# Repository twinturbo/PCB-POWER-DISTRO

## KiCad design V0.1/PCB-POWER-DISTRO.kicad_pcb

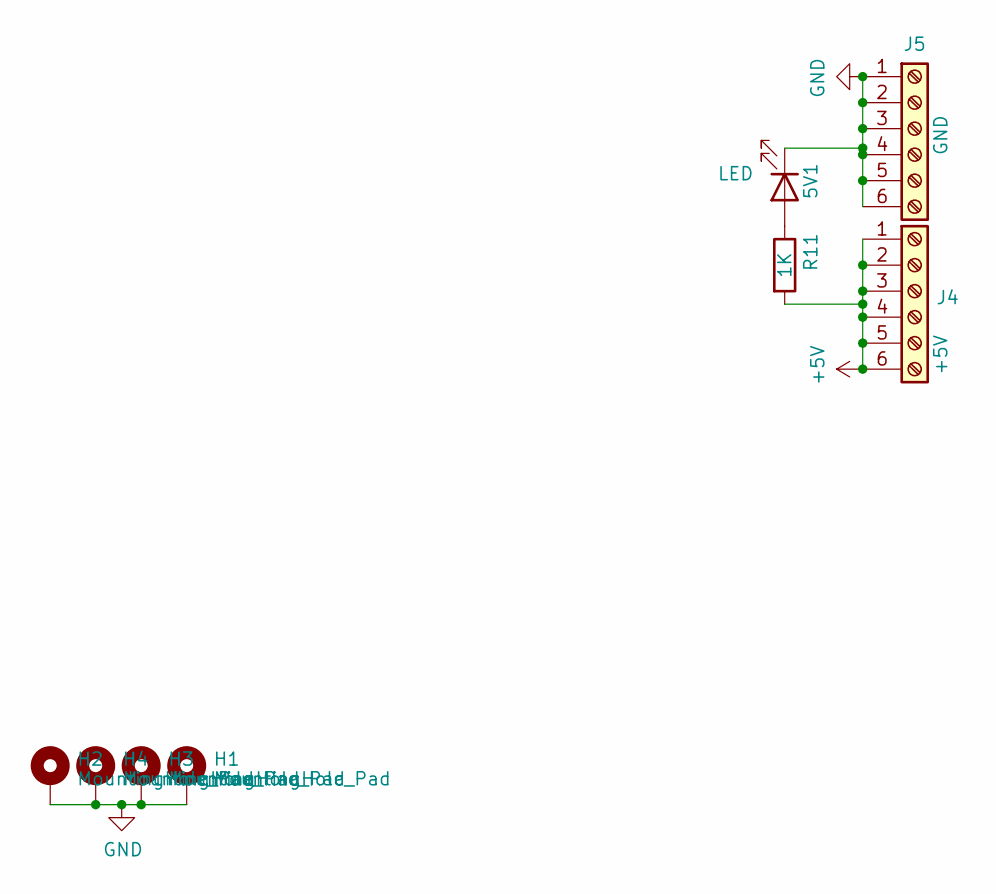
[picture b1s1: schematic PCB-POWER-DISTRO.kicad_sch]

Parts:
5V1: LED; LED_D5.0mm
H1, H2, H3, H4: MountingHole_Pad; MountingHole_3.2mm_M3_DIN965_Pad
J4: +5V; PhoenixContact_MSTBA_2,5_6-G-5,08_1x06_P5.08mm_Horizontal
J5: GND; PhoenixContact_MSTBA_2,5_6-G-5,08_1x06_P5.08mm_Horizontal
R11: 1K; R_Axial_DIN0309_L9.0mm_D3.2mm_P2.54mm_Vertical

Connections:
+5V: J4.1, J4.2, J4.3, J4.4, J4.5, J4.6, R11.2
GND: 5V1.1 (K), H1.1, H2.1, H3.1, H4.1, J5.1, J5.2, J5.3, J5.4, J5.5, J5.6
unnamed: 5V1.2 (A), R11.1

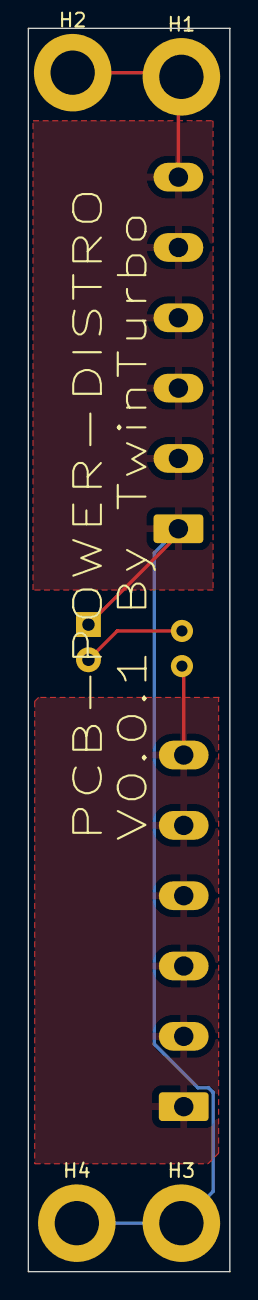
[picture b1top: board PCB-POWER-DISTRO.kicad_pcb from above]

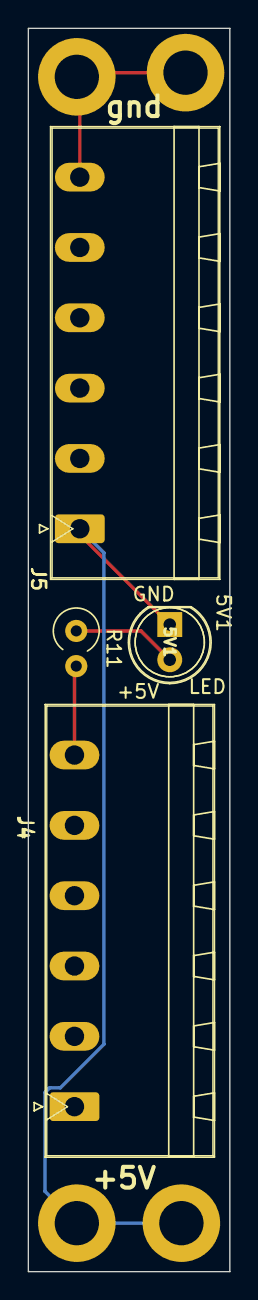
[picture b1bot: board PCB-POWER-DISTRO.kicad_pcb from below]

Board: 2 copper layers, 14.6 x 89.8 mm, 8 parts (4 on the bottom side), 3 nets.

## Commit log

2025-05-12 Initialised
2025-11-12 MAINSYNC
